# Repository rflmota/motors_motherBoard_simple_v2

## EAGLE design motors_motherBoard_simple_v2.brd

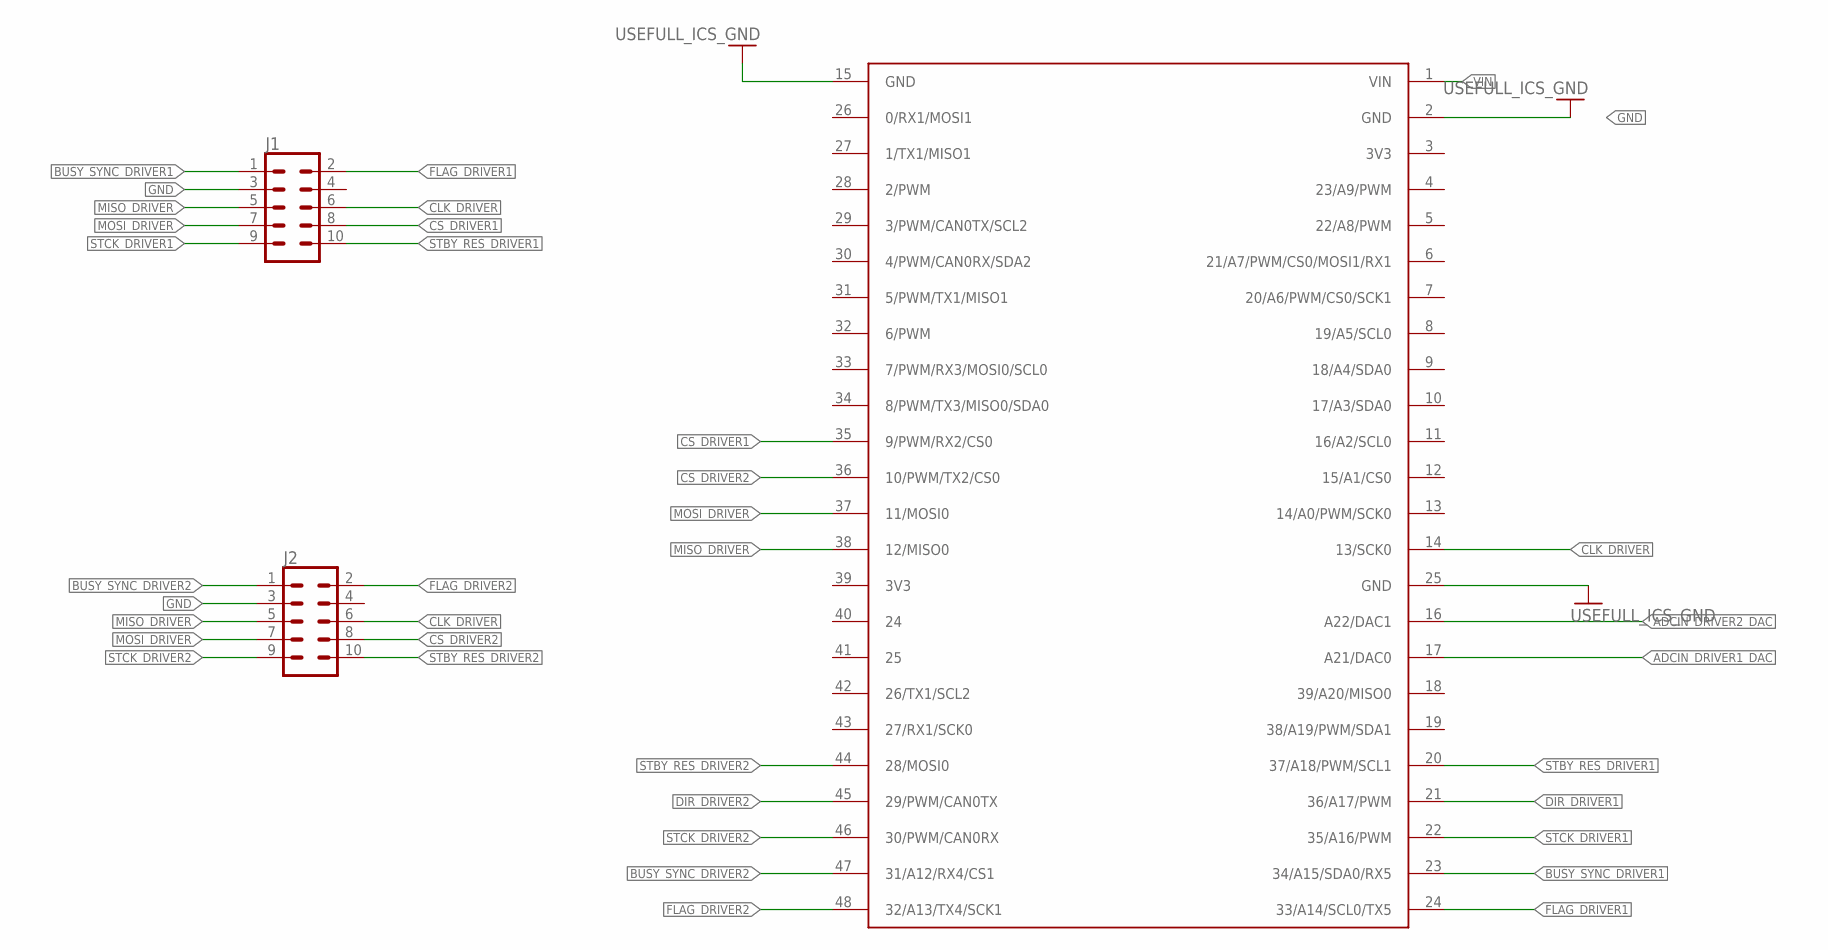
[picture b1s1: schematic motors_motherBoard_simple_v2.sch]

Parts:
J1, J2: SPARKFUN-CONNECTORS_CONN_05X2SHD_LOCK; SPARKFUN-CONNECTORS_2X5-SHROUDED_LOCK
U$3: USEFULL_ICS_TEENSY_BASE_ADAPTER

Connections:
ADCIN_DRIVER1_DAC: U$3.17 (A21/DAC0)
ADCIN_DRIVER2_DAC: U$3.16 (A22/DAC1)
BUSY_SYNC_DRIVER1: J1.1, U$3.23 (34/A15/SDA0/RX5)
BUSY_SYNC_DRIVER2: J2.1, U$3.47 (31/A12/RX4/CS1)
CLK_DRIVER: J1.6, J2.6, U$3.14 (13/SCK0)
CS_DRIVER1: J1.8, U$3.35 (9/PWM/RX2/CS0)
CS_DRIVER2: J2.8, U$3.36 (10/PWM/TX2/CS0)
DIR_DRIVER1: U$3.21 (36/A17/PWM)
DIR_DRIVER2: U$3.45 (29/PWM/CAN0TX)
FLAG_DRIVER1: J1.2, U$3.24 (33/A14/SCL0/TX5)
FLAG_DRIVER2: J2.2, U$3.48 (32/A13/TX4/SCK1)
GND: J1.3, J2.3, U$3.2 (GND), U$3.15 (GND), U$3.25 (GND)
MISO_DRIVER: J1.5, J2.5, U$3.38 (12/MISO0)
MOSI_DRIVER: J1.7, J2.7, U$3.37 (11/MOSI0)
STBY_RES_DRIVER1: J1.10, U$3.20 (37/A18/PWM/SCL1)
STBY_RES_DRIVER2: J2.10, U$3.44 (28/MOSI0)
STCK_DRIVER1: J1.9, U$3.22 (35/A16/PWM)
STCK_DRIVER2: J2.9, U$3.46 (30/PWM/CAN0RX)
VIN: U$3.1 (VIN)

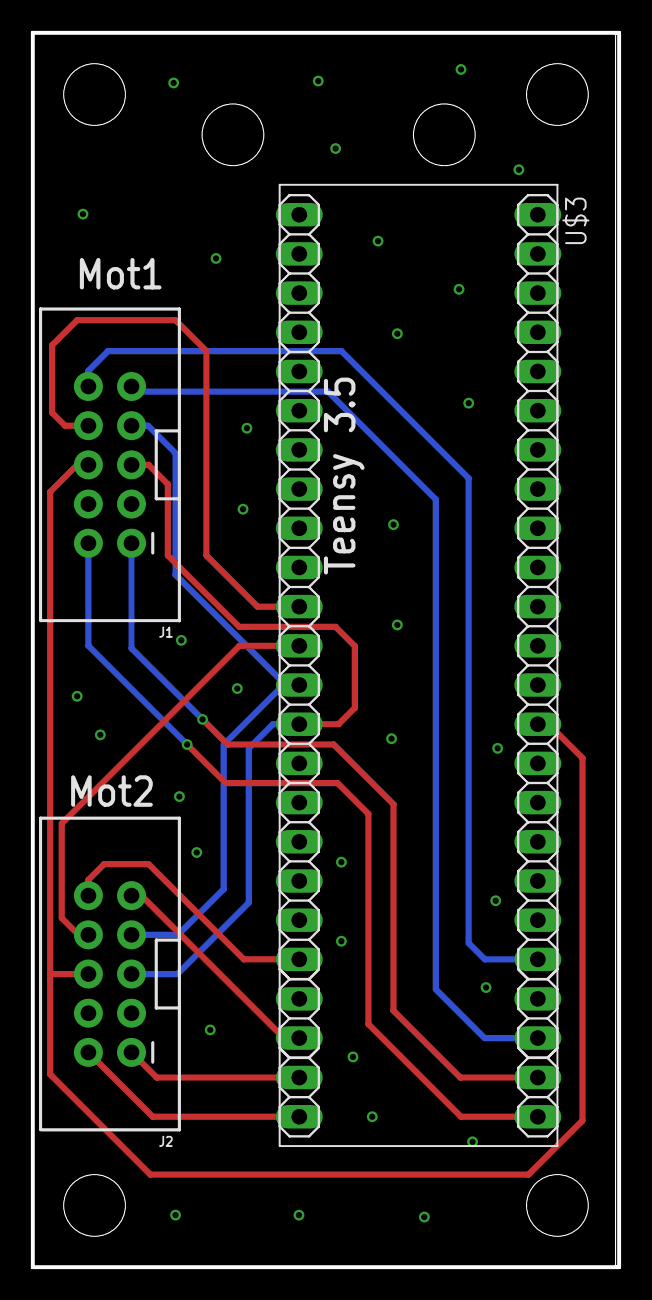
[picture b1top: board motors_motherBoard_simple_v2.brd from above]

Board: 2 copper layers, 38.0 x 80.0 mm, 3 parts (0 on the bottom side), 14 nets.
